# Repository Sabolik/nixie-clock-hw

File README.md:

# HW

- ESP32-C3 MCU
- DC/DC, non-isolated PWM power converter
- USB-C 5V power input

- up to 6 nixie tubes

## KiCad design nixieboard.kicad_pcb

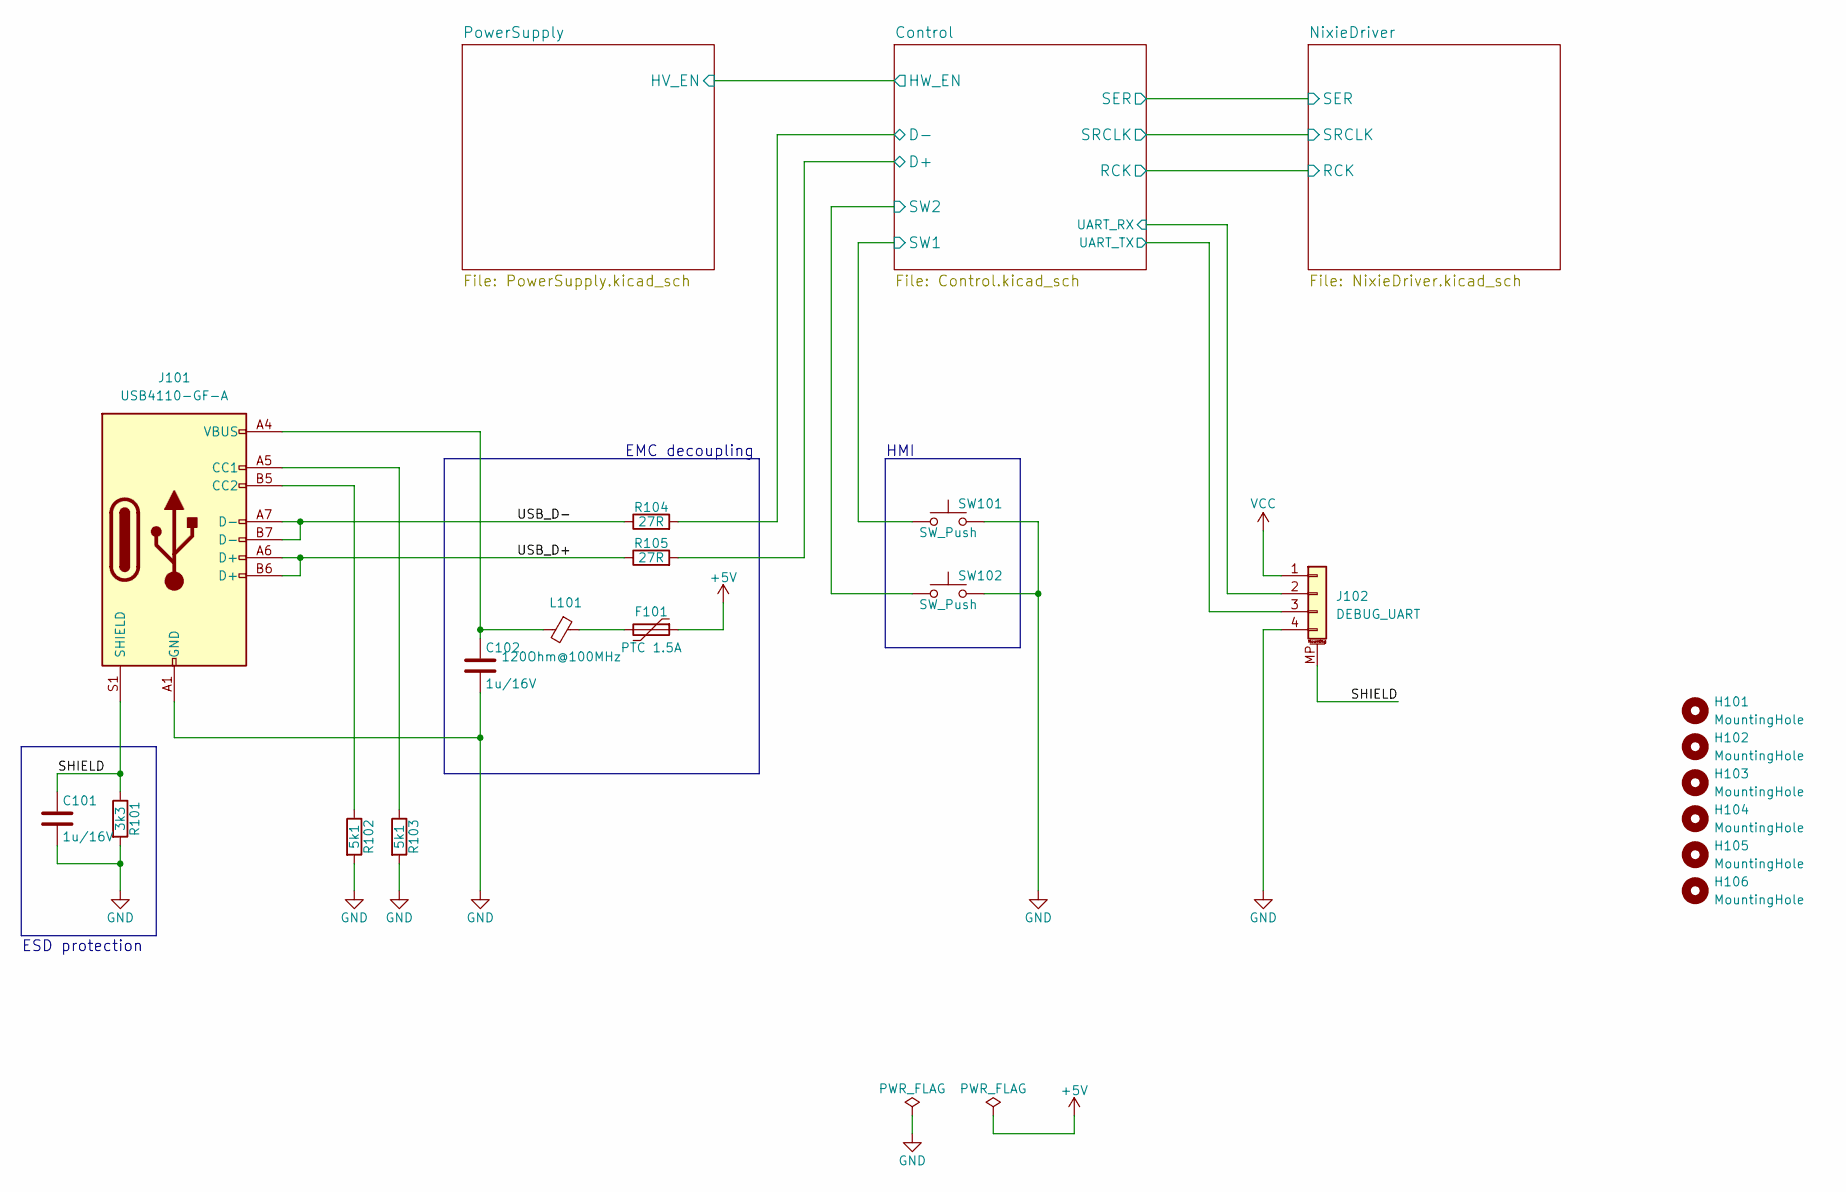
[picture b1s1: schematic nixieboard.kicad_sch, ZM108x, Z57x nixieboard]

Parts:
C101, C102: 1u/16V; C_0805_2012Metric
F101: PTC 1.5A; R_1812_4532Metric
H101, H102, H103, H104, H105, H106: MountingHole; MountingHole_3.2mm_M3
J101: USB4110-GF-A; USB_C_Receptacle_GCT_USB4110
J102: DEBUG_UART; Molex_PicoBlade_53261-0471_1x04-1MP_P1.25mm_Horizontal
L101: 120Ohm@100MHz; L_0805_2012Metric
R101: 3k3; R_0805_2012Metric
R102, R103: 5k1; R_0805_2012Metric
R104, R105: 27R; R_0805_2012Metric
SW101, SW102: SW_Push; SW_SPST_PTS645

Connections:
+5V: F101.1; also elsewhere on the board
/Control/D+: R105.2; also elsewhere on the board
/Control/D-: R104.2; also elsewhere on the board
/Control/SW1: SW101.1; also elsewhere on the board
/Control/SW2: SW102.1; also elsewhere on the board
/Control/UART_RX: J102.2; also elsewhere on the board
/Control/UART_TX: J102.3; also elsewhere on the board
/SHIELD: C101.1, J101.S1 (SHIELD), J102.MP (MountPin), R101.1
/USB_D+: J101.A6 (D+), J101.B6 (D+), R105.1
/USB_D-: J101.A7 (D-), J101.B7 (D-), R104.1
GND: C101.2, C102.2, J101.A1 (GND), J101.A12 (GND), J101.B1 (GND), J101.B12 (GND), J102.4, R101.2, R102.2, R103.2, SW101.2, SW102.2; also elsewhere on the board
unnamed: C102.1, J101.A4 (VBUS), J101.A9 (VBUS), J101.B4 (VBUS), J101.B9 (VBUS), L101.2
unnamed: F101.2, L101.1
unnamed: J101.A5 (CC1), R103.1
unnamed: J101.B5 (CC2), R102.1
VCC: J102.1; also elsewhere on the board

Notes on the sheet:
EMC decoupling
ESD protection
HMI

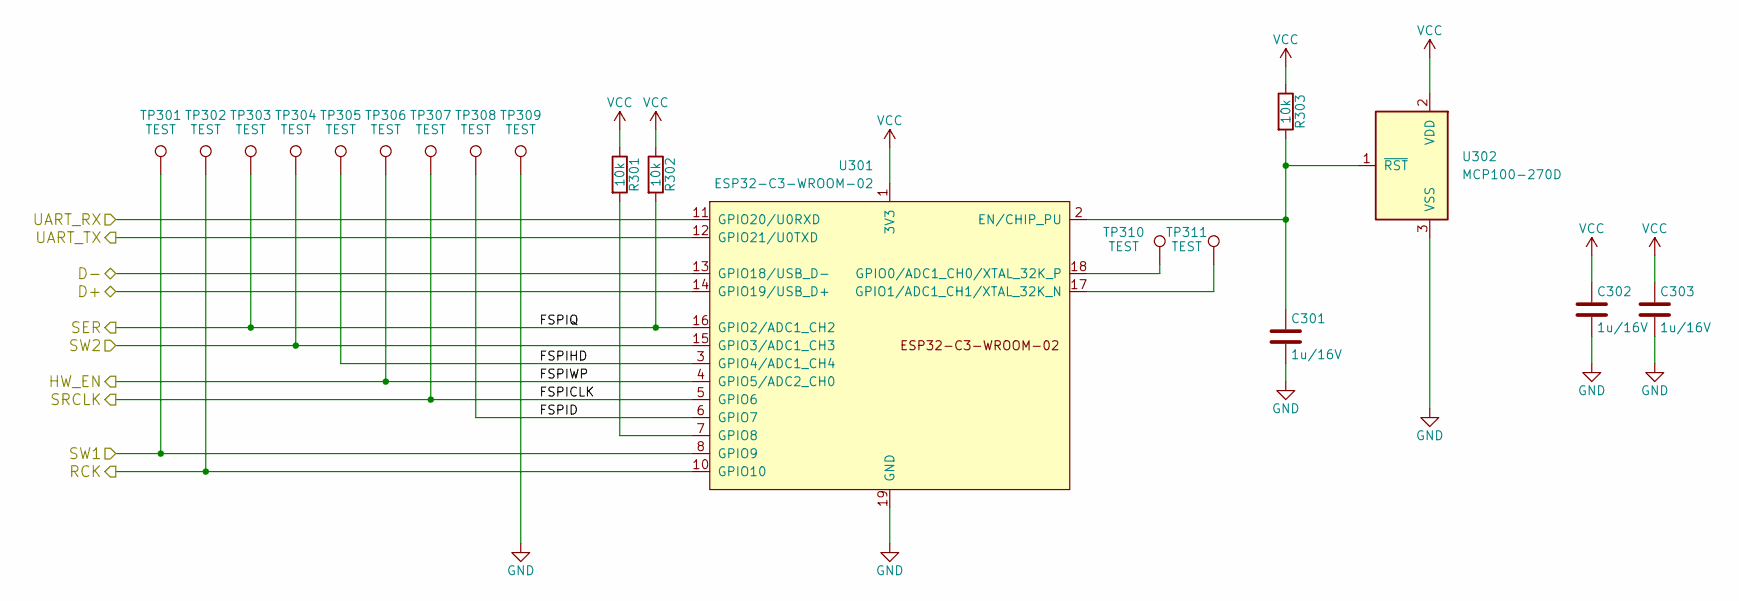
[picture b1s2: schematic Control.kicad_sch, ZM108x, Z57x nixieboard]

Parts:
C301, C302, C303: 1u/16V; C_0805_2012Metric
R301, R302, R303: 10k; R_0805_2012Metric
TP301, TP302, TP303, TP304, TP305, TP306, TP307, TP308, TP309, TP310, TP311: TEST; TestPoint_Pad_D1.5mm
U301: ESP32-C3-WROOM-02
U302: MCP100-270D; SOT-23-3

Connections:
/Control/D+: U301.14 (GPIO19/USB_D+); also elsewhere on the board
/Control/D-: U301.13 (GPIO18/USB_D-); also elsewhere on the board
/Control/FSPICLK: TP307.1, U301.5 (GPIO6); also elsewhere on the board
/Control/FSPID: TP308.1, U301.6 (GPIO7)
/Control/FSPIHD: TP305.1, U301.3 (GPIO4/ADC1_CH4)
/Control/FSPIQ: R302.2, TP303.1, U301.16 (GPIO2/ADC1_CH2); also elsewhere on the board
/Control/FSPIWP: TP306.1, U301.4 (GPIO5/ADC2_CH0); also elsewhere on the board
/Control/RCK: TP302.1, U301.10 (GPIO10); also elsewhere on the board
/Control/SW1: TP301.1, U301.8 (GPIO9); also elsewhere on the board
/Control/SW2: TP304.1, U301.15 (GPIO3/ADC1_CH3); also elsewhere on the board
/Control/UART_RX: U301.11 (GPIO20/U0RXD); also elsewhere on the board
/Control/UART_TX: U301.12 (GPIO21/U0TXD); also elsewhere on the board
GND: C301.2, C302.2, C303.2, TP309.1, U301.9 (GND), U301.19 (GND), U302.3 (VSS); also elsewhere on the board
unnamed: C301.1, R303.2, U301.2 (EN/CHIP_PU), U302.1 (~RST)
unnamed: TP310.1, U301.18 (GPIO0/ADC1_CH0/XTAL_32K_P)
unnamed: TP311.1, U301.17 (GPIO1/ADC1_CH1/XTAL_32K_N)
unnamed: R301.2, U301.7 (GPIO8)
VCC: C302.1, C303.1, R301.1, R302.1, R303.1, U301.1 (3V3), U302.2 (VDD); also elsewhere on the board

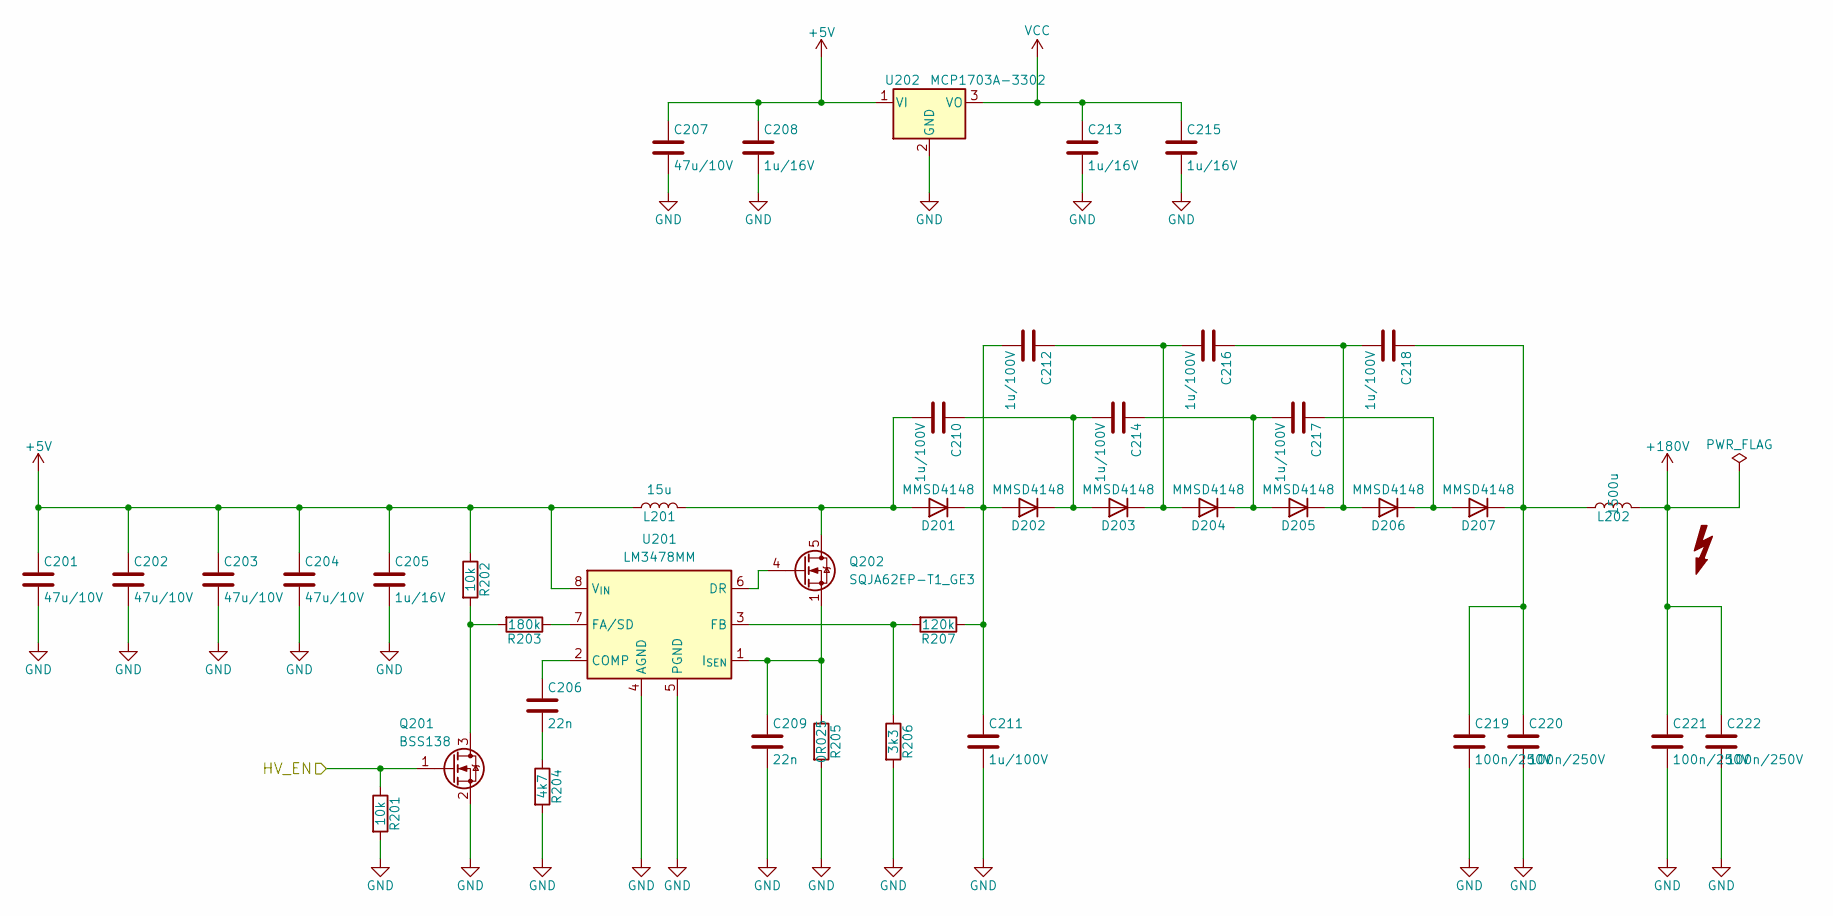
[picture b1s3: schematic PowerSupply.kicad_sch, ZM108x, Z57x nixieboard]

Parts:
C201, C202, C203, C204, C207: 47u/10V; C_1206_3216Metric
C205, C208, C213, C215: 1u/16V; C_0805_2012Metric
C206, C209: 22n; C_0805_2012Metric
C210, C211, C212, C214, C216, C217, C218: 1u/100V; C_1206_3216Metric
C219, C220, C221, C222: 100n/250V; C_1206_3216Metric
D201, D202, D203, D204, D205, D206, D207: MMSD4148; D_SOD-123
L201: 15u; L_Bourns_SRR1208_12.7x12.7mm
L202: 1500u; L_1812_4532Metric
Q201: BSS138; SOT-23
Q202: SQJA62EP-T1_GE3; PowerPAK_SO-8_Single
R201, R202: 10k; R_0805_2012Metric
R203: 180k; R_0805_2012Metric
R204: 4k7; R_0805_2012Metric
R205: 0R025; R_0805_2012Metric
R206: 3k3; R_0805_2012Metric
R207: 120k; R_0805_2012Metric
U201: LM3478MM; VSSOP-8_3.0x3.0mm_P0.65mm
U202: MCP1703A-3302; SOT-223-3_TabPin2

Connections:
+5V: C201.1, C202.1, C203.1, C204.1, C205.1, C207.1, C208.1, L201.1, R202.1, U201.8 (V_{IN}), U202.1 (VI); also elsewhere on the board
/Control/FSPIWP: Q201.1 (G), R201.1; also elsewhere on the board
GND: C201.2, C202.2, C203.2, C204.2, C205.2, C207.2, C208.2, C209.2, C211.2, C213.2, C215.2, C219.2, C220.2, C221.2, C222.2, Q201.2 (S), R201.2, R204.2, R205.2, R206.2, U201.4 (AGND), U201.5 (PGND), U202.2 (GND); also elsewhere on the board
unnamed: C206.2, R204.1
unnamed: C210.2, D201.2 (A), L201.2, Q202.5 (D)
unnamed: C211.1, C212.2, D201.1 (K), D202.2 (A), R207.1
unnamed: C210.1, C214.2, D202.1 (K), D203.2 (A)
unnamed: C212.1, C216.2, D203.1 (K), D204.2 (A)
unnamed: C214.1, C217.2, D204.1 (K), D205.2 (A)
unnamed: C216.1, C218.2, D205.1 (K), D206.2 (A)
unnamed: C217.1, D206.1 (K), D207.2 (A)
unnamed: C218.1, C219.1, C220.1, D207.1 (K), L202.1
unnamed: Q201.3 (D), R202.2, R203.2
unnamed: Q202.4 (G), U201.6 (DR)
unnamed: C206.1, U201.2 (COMP)
unnamed: R203.1, U201.7 (FA/SD)
unnamed: R206.1, R207.2, U201.3 (FB)
unnamed: C209.1, Q202.1 (S), Q202.2 (S), Q202.3 (S), R205.1, U201.1 (I_{SEN})
VCC: C213.1, C215.1, U202.3 (VO); also elsewhere on the board
Vdrive: C221.1, C222.1, L202.2; also elsewhere on the board

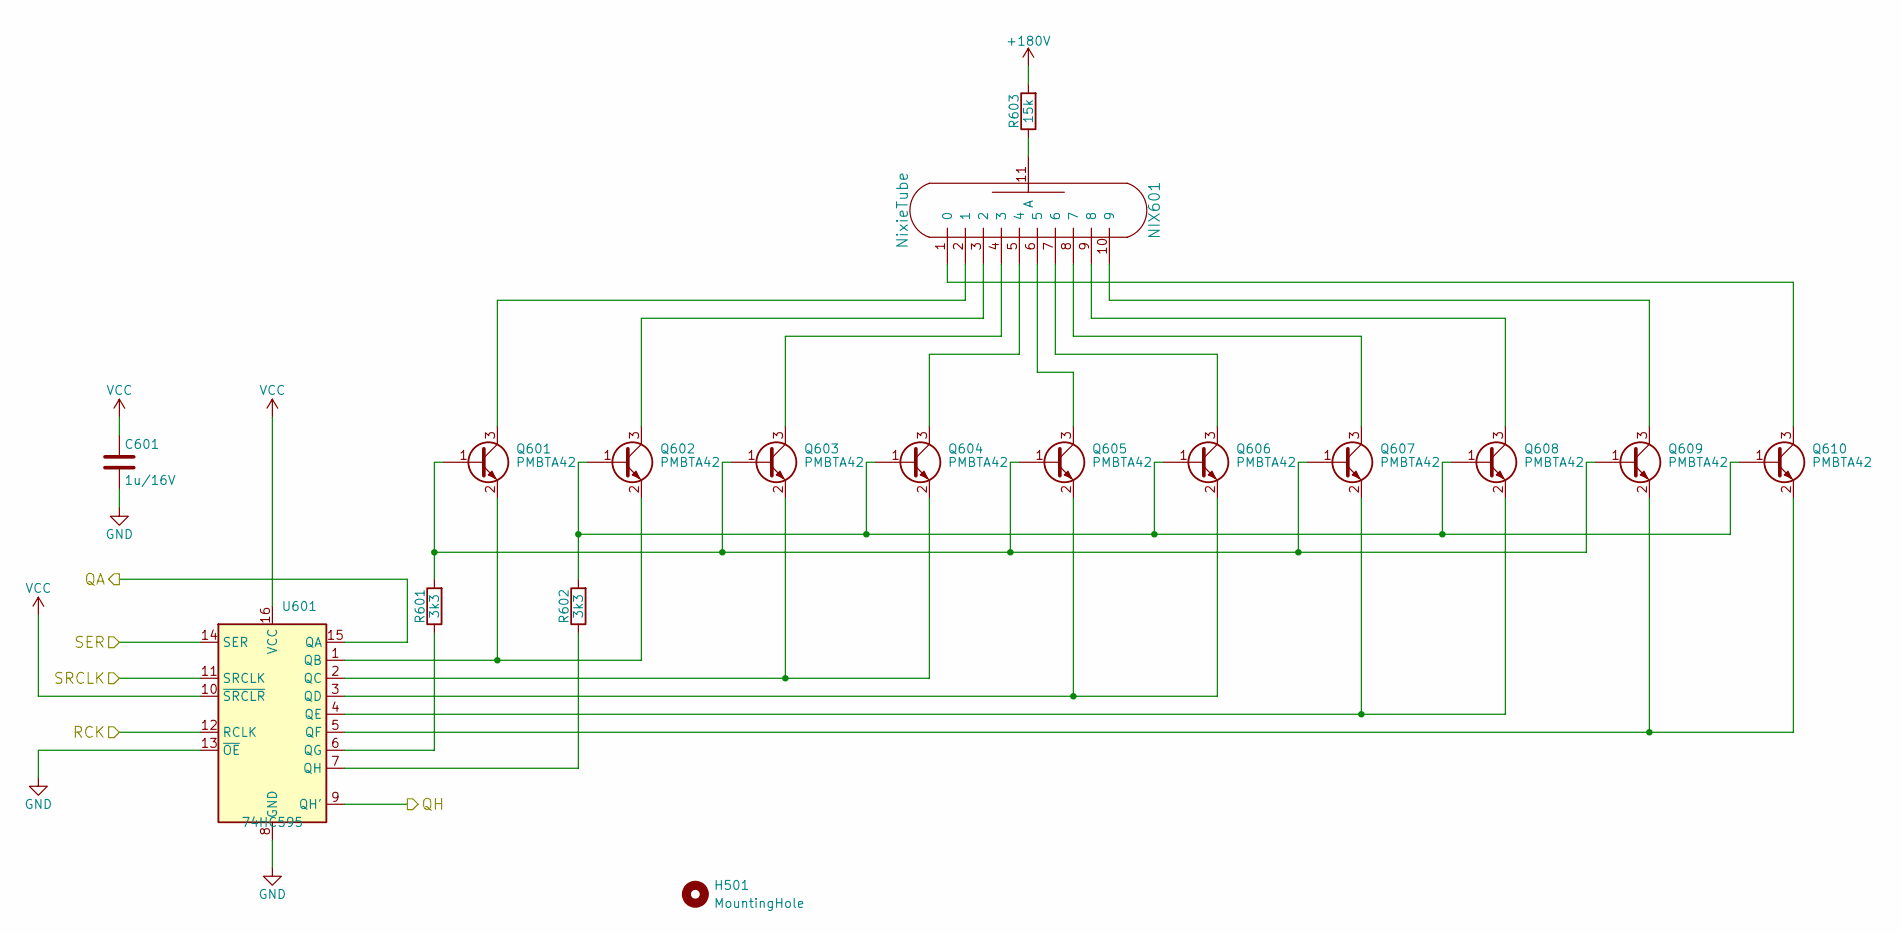
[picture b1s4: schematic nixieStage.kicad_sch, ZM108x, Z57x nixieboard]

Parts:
C601: 1u/16V; C_0805_2012Metric
H501: MountingHole; MountingHole_5.3mm_M5
NIX601: NixieTube; Zxxx
Q601, Q602, Q603, Q604, Q605, Q606, Q607, Q608, Q609, Q610: PMBTA42; SOT-23
R601, R602: 3k3; R_0603_1608Metric
R603: 15k; R_1206_3216Metric
U601: 74HC595; TSSOP-16_4.4x5mm_P0.65mm

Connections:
/Control/FSPICLK: U601.11 (SRCLK); also elsewhere on the board
/Control/RCK: U601.12 (RCLK); also elsewhere on the board
/NixieDriver/neon0/NEON: U601.15 (QA); also elsewhere on the board
/NixieDriver/nixieStage0/QH: U601.14 (SER); also elsewhere on the board
/NixieDriver/nixieStage1/QH: U601.9 (QH'); also elsewhere on the board
GND: C601.2, U601.8 (GND), U601.13 (~OE); also elsewhere on the board
unnamed: NIX601.1 (0), Q610.3 (C)
unnamed: NIX601.2 (1), Q601.3 (C)
unnamed: NIX601.3 (2), Q602.3 (C)
unnamed: NIX601.4 (3), Q603.3 (C)
unnamed: NIX601.5 (4), Q604.3 (C)
unnamed: NIX601.6 (5), Q605.3 (C)
unnamed: NIX601.7 (6), Q606.3 (C)
unnamed: NIX601.8 (7), Q607.3 (C)
unnamed: NIX601.9 (8), Q608.3 (C)
unnamed: NIX601.10 (9), Q609.3 (C)
unnamed: NIX601.11 (A), R603.1
unnamed: Q601.1 (B), Q603.1 (B), Q605.1 (B), Q607.1 (B), Q609.1 (B), R601.2
unnamed: Q601.2 (E), Q602.2 (E), U601.1 (QB)
unnamed: Q602.1 (B), Q604.1 (B), Q606.1 (B), Q608.1 (B), Q610.1 (B), R602.2
unnamed: Q603.2 (E), Q604.2 (E), U601.2 (QC)
unnamed: Q605.2 (E), Q606.2 (E), U601.3 (QD)
unnamed: Q607.2 (E), Q608.2 (E), U601.4 (QE)
unnamed: Q609.2 (E), Q610.2 (E), U601.5 (QF)
unnamed: R601.1, U601.6 (QG)
unnamed: R602.1, U601.7 (QH)
VCC: C601.1, U601.10 (~SRCLR), U601.16 (VCC); also elsewhere on the board
Vdrive: R603.2; also elsewhere on the board

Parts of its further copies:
C501, C701, C901, C1001, C1201: 1u/16V; C_0805_2012Metric
H601, H701, H901, H1001, H1201: MountingHole; MountingHole_5.3mm_M5
NIX501, NIX701, NIX901, NIX1001, NIX1201: NixieTube; Zxxx
Q501, Q502, Q503, Q504, Q505, Q506, Q507, Q508, Q509, Q510, Q701, Q702, Q703, Q704, Q705, Q706, Q707, Q708, Q709, Q710, Q901, Q902, Q903, Q904, Q905, Q906, Q907, Q908, Q909, Q910, Q1001, Q1002, Q1003, Q1004, Q1005, Q1006, Q1007, Q1008, Q1009, Q1010, Q1201, Q1202, Q1203, Q1204, Q1205, Q1206, Q1207, Q1208, Q1209, Q1210: PMBTA42; SOT-23
R501, R502, R701, R702, R901, R902, R1001, R1002, R1201, R1202: 3k3; R_0603_1608Metric
R503, R703, R903, R1003, R1203: 15k; R_1206_3216Metric
U501, U701, U901, U1001, U1201: 74HC595; TSSOP-16_4.4x5mm_P0.65mm

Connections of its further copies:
/Control/FSPICLK: U501.11 (SRCLK), U701.11 (SRCLK), U901.11 (SRCLK), U1001.11 (SRCLK), U1201.11 (SRCLK); also elsewhere on the board
/Control/FSPIQ: U501.14 (SER); also elsewhere on the board
/Control/RCK: U501.12 (RCLK), U701.12 (RCLK), U901.12 (RCLK), U1001.12 (RCLK), U1201.12 (RCLK); also elsewhere on the board
/NixieDriver/neon1/NEON: U901.15 (QA); also elsewhere on the board
/NixieDriver/nixieStage0/QA: U501.15 (QA)
/NixieDriver/nixieStage0/QH: U501.9 (QH'); also elsewhere on the board
/NixieDriver/nixieStage1/QH: U701.14 (SER); also elsewhere on the board
/NixieDriver/nixieStage2/QA: U701.15 (QA)
/NixieDriver/nixieStage2/QH: U701.9 (QH'), U901.14 (SER)
/NixieDriver/nixieStage3/QH: U901.9 (QH'), U1001.14 (SER)
/NixieDriver/nixieStage4/QA: U1001.15 (QA)
/NixieDriver/nixieStage4/QH: U1001.9 (QH'), U1201.14 (SER)
/NixieDriver/nixieStage5/QA: U1201.15 (QA)
/NixieDriver/nixieStage5/QH: U1201.9 (QH')
GND: C501.2, C701.2, C901.2, C1001.2, C1201.2, U501.8 (GND), U501.13 (~OE), U701.8 (GND), U701.13 (~OE), U901.8 (GND), U901.13 (~OE), U1001.8 (GND), U1001.13 (~OE), U1201.8 (GND), U1201.13 (~OE); also elsewhere on the board
unnamed: NIX501.1 (0), Q510.3 (C)
unnamed: NIX501.2 (1), Q501.3 (C)
unnamed: NIX501.3 (2), Q502.3 (C)
unnamed: NIX501.4 (3), Q503.3 (C)
unnamed: NIX501.5 (4), Q504.3 (C)
unnamed: NIX501.6 (5), Q505.3 (C)
unnamed: NIX501.7 (6), Q506.3 (C)
unnamed: NIX501.8 (7), Q507.3 (C)
unnamed: NIX501.9 (8), Q508.3 (C)
unnamed: NIX501.10 (9), Q509.3 (C)
unnamed: NIX501.11 (A), R503.1
unnamed: NIX701.1 (0), Q710.3 (C)
unnamed: NIX701.2 (1), Q701.3 (C)
unnamed: NIX701.3 (2), Q702.3 (C)
unnamed: NIX701.4 (3), Q703.3 (C)
unnamed: NIX701.5 (4), Q704.3 (C)
unnamed: NIX701.6 (5), Q705.3 (C)
unnamed: NIX701.7 (6), Q706.3 (C)
unnamed: NIX701.8 (7), Q707.3 (C)
unnamed: NIX701.9 (8), Q708.3 (C)
unnamed: NIX701.10 (9), Q709.3 (C)
unnamed: NIX701.11 (A), R703.1
unnamed: NIX901.1 (0), Q910.3 (C)
unnamed: NIX901.2 (1), Q901.3 (C)
unnamed: NIX901.3 (2), Q902.3 (C)
unnamed: NIX901.4 (3), Q903.3 (C)
unnamed: NIX901.5 (4), Q904.3 (C)
unnamed: NIX901.6 (5), Q905.3 (C)
unnamed: NIX901.7 (6), Q906.3 (C)
unnamed: NIX901.8 (7), Q907.3 (C)
unnamed: NIX901.9 (8), Q908.3 (C)
unnamed: NIX901.10 (9), Q909.3 (C)
unnamed: NIX901.11 (A), R903.1
unnamed: NIX1001.1 (0), Q1010.3 (C)
unnamed: NIX1001.2 (1), Q1001.3 (C)
unnamed: NIX1001.3 (2), Q1002.3 (C)
unnamed: NIX1001.4 (3), Q1003.3 (C)
unnamed: NIX1001.5 (4), Q1004.3 (C)
unnamed: NIX1001.6 (5), Q1005.3 (C)
unnamed: NIX1001.7 (6), Q1006.3 (C)
unnamed: NIX1001.8 (7), Q1007.3 (C)
unnamed: NIX1001.9 (8), Q1008.3 (C)
unnamed: NIX1001.10 (9), Q1009.3 (C)
unnamed: NIX1001.11 (A), R1003.1
unnamed: NIX1201.1 (0), Q1210.3 (C)
unnamed: NIX1201.2 (1), Q1201.3 (C)
unnamed: NIX1201.3 (2), Q1202.3 (C)
unnamed: NIX1201.4 (3), Q1203.3 (C)
unnamed: NIX1201.5 (4), Q1204.3 (C)
unnamed: NIX1201.6 (5), Q1205.3 (C)
unnamed: NIX1201.7 (6), Q1206.3 (C)
unnamed: NIX1201.8 (7), Q1207.3 (C)
unnamed: NIX1201.9 (8), Q1208.3 (C)
unnamed: NIX1201.10 (9), Q1209.3 (C)
unnamed: NIX1201.11 (A), R1203.1
unnamed: Q501.1 (B), Q503.1 (B), Q505.1 (B), Q507.1 (B), Q509.1 (B), R501.2
unnamed: Q501.2 (E), Q502.2 (E), U501.1 (QB)
unnamed: Q502.1 (B), Q504.1 (B), Q506.1 (B), Q508.1 (B), Q510.1 (B), R502.2
unnamed: Q503.2 (E), Q504.2 (E), U501.2 (QC)
unnamed: Q505.2 (E), Q506.2 (E), U501.3 (QD)
unnamed: Q507.2 (E), Q508.2 (E), U501.4 (QE)
unnamed: Q509.2 (E), Q510.2 (E), U501.5 (QF)
unnamed: Q701.1 (B), Q703.1 (B), Q705.1 (B), Q707.1 (B), Q709.1 (B), R701.2
unnamed: Q701.2 (E), Q702.2 (E), U701.1 (QB)
unnamed: Q702.1 (B), Q704.1 (B), Q706.1 (B), Q708.1 (B), Q710.1 (B), R702.2
unnamed: Q703.2 (E), Q704.2 (E), U701.2 (QC)
unnamed: Q705.2 (E), Q706.2 (E), U701.3 (QD)
unnamed: Q707.2 (E), Q708.2 (E), U701.4 (QE)
unnamed: Q709.2 (E), Q710.2 (E), U701.5 (QF)
unnamed: Q901.1 (B), Q903.1 (B), Q905.1 (B), Q907.1 (B), Q909.1 (B), R901.2
unnamed: Q901.2 (E), Q902.2 (E), U901.1 (QB)
unnamed: Q902.1 (B), Q904.1 (B), Q906.1 (B), Q908.1 (B), Q910.1 (B), R902.2
unnamed: Q903.2 (E), Q904.2 (E), U901.2 (QC)
unnamed: Q905.2 (E), Q906.2 (E), U901.3 (QD)
unnamed: Q907.2 (E), Q908.2 (E), U901.4 (QE)
unnamed: Q909.2 (E), Q910.2 (E), U901.5 (QF)
unnamed: Q1001.1 (B), Q1003.1 (B), Q1005.1 (B), Q1007.1 (B), Q1009.1 (B), R1001.2
unnamed: Q1001.2 (E), Q1002.2 (E), U1001.1 (QB)
unnamed: Q1002.1 (B), Q1004.1 (B), Q1006.1 (B), Q1008.1 (B), Q1010.1 (B), R1002.2
unnamed: Q1003.2 (E), Q1004.2 (E), U1001.2 (QC)
unnamed: Q1005.2 (E), Q1006.2 (E), U1001.3 (QD)
unnamed: Q1007.2 (E), Q1008.2 (E), U1001.4 (QE)
unnamed: Q1009.2 (E), Q1010.2 (E), U1001.5 (QF)
unnamed: Q1201.1 (B), Q1203.1 (B), Q1205.1 (B), Q1207.1 (B), Q1209.1 (B), R1201.2
unnamed: Q1201.2 (E), Q1202.2 (E), U1201.1 (QB)
unnamed: Q1202.1 (B), Q1204.1 (B), Q1206.1 (B), Q1208.1 (B), Q1210.1 (B), R1202.2
unnamed: Q1203.2 (E), Q1204.2 (E), U1201.2 (QC)
unnamed: Q1205.2 (E), Q1206.2 (E), U1201.3 (QD)
unnamed: Q1207.2 (E), Q1208.2 (E), U1201.4 (QE)
unnamed: Q1209.2 (E), Q1210.2 (E), U1201.5 (QF)
unnamed: R501.1, U501.6 (QG)
unnamed: R502.1, U501.7 (QH)
unnamed: R701.1, U701.6 (QG)
unnamed: R702.1, U701.7 (QH)
unnamed: R901.1, U901.6 (QG)
unnamed: R902.1, U901.7 (QH)
unnamed: R1001.1, U1001.6 (QG)
unnamed: R1002.1, U1001.7 (QH)
unnamed: R1201.1, U1201.6 (QG)
unnamed: R1202.1, U1201.7 (QH)
VCC: C501.1, C701.1, C901.1, C1001.1, C1201.1, U501.10 (~SRCLR), U501.16 (VCC), U701.10 (~SRCLR), U701.16 (VCC), U901.10 (~SRCLR), U901.16 (VCC), U1001.10 (~SRCLR), U1001.16 (VCC), U1201.10 (~SRCLR), U1201.16 (VCC); also elsewhere on the board
Vdrive: R503.2, R703.2, R903.2, R1003.2, R1203.2; also elsewhere on the board

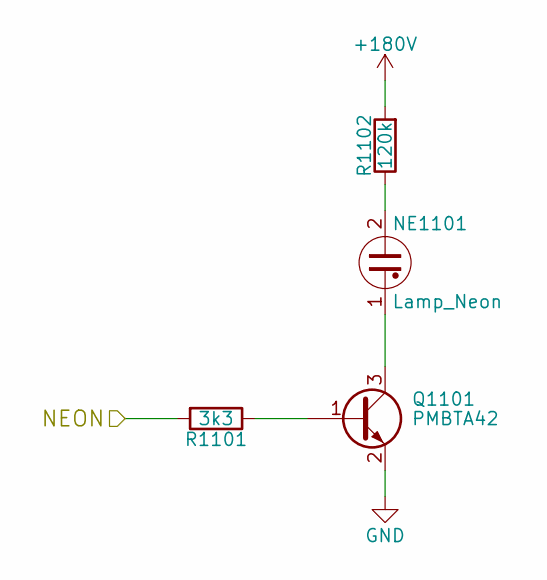
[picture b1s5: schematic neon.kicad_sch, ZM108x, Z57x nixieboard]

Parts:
NE1101: Lamp_Neon; Neon
Q1101: PMBTA42; SOT-23
R1101: 3k3; R_0603_1608Metric
R1102: 120k; R_1206_3216Metric

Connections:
/NixieDriver/neon1/NEON: R1101.2; also elsewhere on the board
GND: Q1101.2 (E); also elsewhere on the board
unnamed: NE1101.2, R1102.1
unnamed: Q1101.1 (B), R1101.1
unnamed: NE1101.1, Q1101.3 (C)
Vdrive: R1102.2; also elsewhere on the board

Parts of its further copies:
NE801: Lamp_Neon; Neon
Q801: PMBTA42; SOT-23
R801: 3k3; R_0603_1608Metric
R802: 120k; R_1206_3216Metric

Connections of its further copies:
/NixieDriver/neon0/NEON: R801.2; also elsewhere on the board
GND: Q801.2 (E); also elsewhere on the board
unnamed: NE801.2, R802.1
unnamed: Q801.1 (B), R801.1
unnamed: NE801.1, Q801.3 (C)
Vdrive: R802.2; also elsewhere on the board

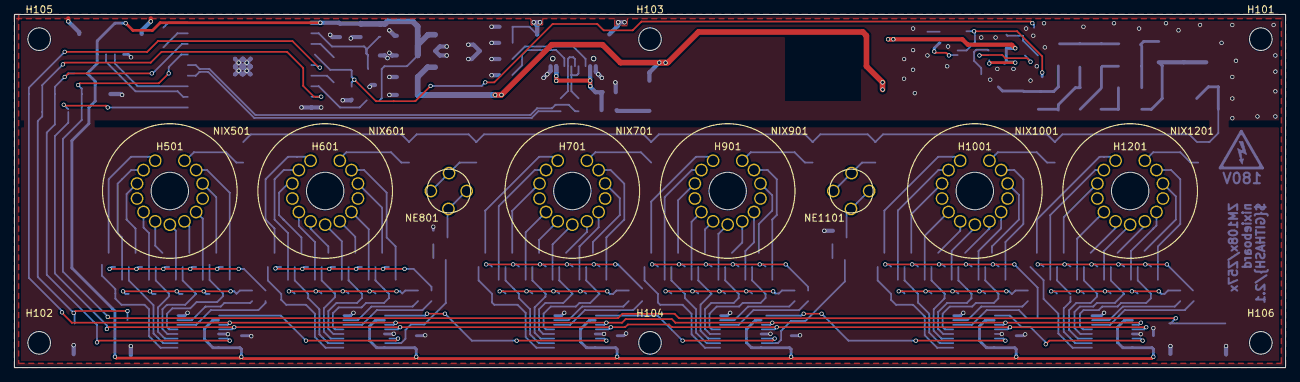
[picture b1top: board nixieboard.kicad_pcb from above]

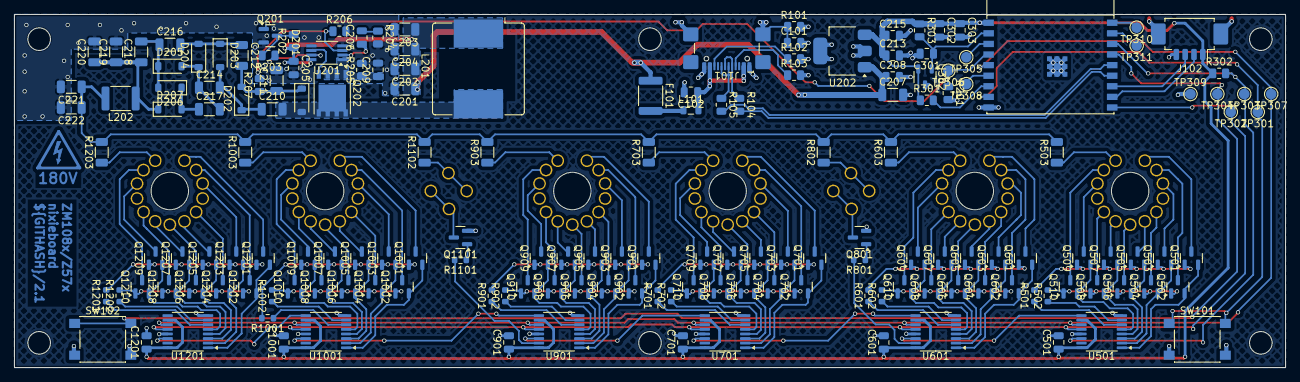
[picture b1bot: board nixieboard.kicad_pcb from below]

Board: 2 copper layers, 180.0 x 50.0 mm, 190 parts (170 on the bottom side), 175 nets.

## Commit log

2025-09-04 rev 2: new revision ready for manufacturing.
    Main updates:
    - switch to KiCad7
    - ESP8266 replaced with ESP32-C3
    - DCDC controler replaced
    - remove un-used capatitors
2025-09-04 ci: add kibod project configuration
2025-09-04 ci: fix kibot preflight config
2025-09-04 ci: auto run action when tag is created
2025-09-04 add git hash
2025-09-04 ci: add artifacts to release
2025-09-05 CI: run ERC/DRC triggered by schematic/pcb update.
2025-09-05 ci: compress all doc data generated by kibot
2025-09-05 ci: generate project archive artifacts
2025-09-05 ci: enable drc
2025-09-05 ci: drc check update
2025-09-05 ci: use run_drc, run_erc kibot options
2025-09-05 pcb: add drc solder mask bridge violation to be ignored
2025-09-05 doc: add ci status to readme
2025-09-05 doc: add current release PCB render to readme
2025-09-06 doc: add basic description
2025-09-06 schema: bom: PNs update
2026-02-27 BoM: optimize parts
2026-02-27 pcb: fix HV generator enable input
2026-02-27 Update README with latest PCB render and formatting
